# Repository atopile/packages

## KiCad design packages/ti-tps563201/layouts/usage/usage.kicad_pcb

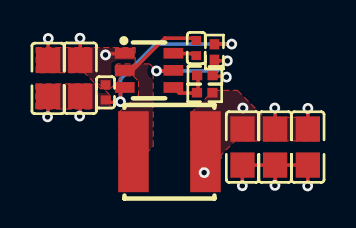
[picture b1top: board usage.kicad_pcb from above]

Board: 2 copper layers, 12 parts (0 on the bottom side), 7 nets.

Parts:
C1, C4: 100nF ±10%; C0402
C2, C3, C5, C6, C7: 10µF ±10%; C0805
L1: L 2.2µH ±20%; IND-SMD_L5.0-W5.0_FNR5012S
R1: 10kΩ ±1%; R0402
R2: 10.2kΩ ±1%; R0402
R3: 3.09kΩ ±1%; R0402
U1: SOT-23-6_L2.9-W1.6-P0.95-LS2.8-BR

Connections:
EN: R1.1, U1.5
hv: C1.1, U1.6
input_caps[2]-power-hv: C2.1, C3.1, C4.1, R1.2, U1.3
lv: C1.2, L1.1, U1.2
output_caps[2]-power-hv: C5.1, C6.1, C7.1, L1.2, R2.1
output_caps[2]-power-lv: C2.2, C3.2, C4.2, C5.2, C6.2, C7.2, R3.2, U1.1
ref_out-hv: R2.2, R3.1, U1.4

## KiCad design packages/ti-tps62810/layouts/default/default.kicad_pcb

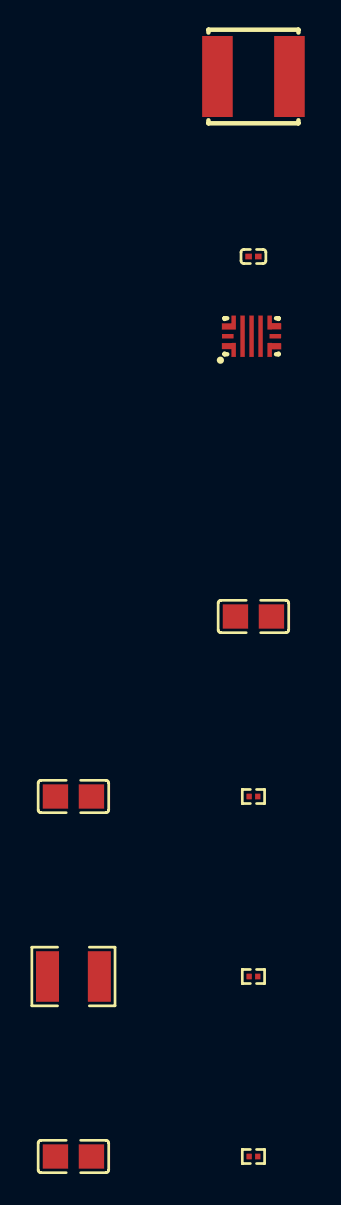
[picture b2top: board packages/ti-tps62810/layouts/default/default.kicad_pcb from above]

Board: 2 copper layers, 10 parts (0 on the bottom side), 7 nets, no tracks yet.

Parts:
C1, C2, C3: 0F; C0805
C4: 0F; C0201
L1: L 0H; IND-SMD_L5.0-W5.0_FNR5012S
R1, R2: 100000Ω; R0201
R3: 200000Ω; R0201
R4: 75Ω; R1210
U1: VQFN-HR-9_L3.0-W2.0-P0.50-BL_TI_TPS6281XXXXX

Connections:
EN: R1.2, U1.8
FB: R2.1, R3.2, U1.5
SW: L1.1, U1.3
hv: C1.1, R1.1, U1.2
lv: C1.2, C2.2, C3.2, C4.2, R2.2, R4.2, U1.4, U1.7
output_cap2-power-hv: C2.1, C3.1, L1.2, R3.1, R4.1
soft_start_cap-power-hv: C4.1, U1.6

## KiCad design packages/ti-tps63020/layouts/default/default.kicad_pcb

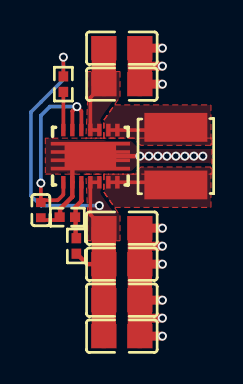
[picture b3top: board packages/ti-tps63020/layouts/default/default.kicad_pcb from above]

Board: 2 copper layers, 12 parts (0 on the bottom side), 9 nets.

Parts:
C1, C2: 10µF ±10%; C0805
C3, C4, C5, C6: 22µF ±20%; C0805
C7: 100nF ±10%; C0402
L1: L 1µH ±20%; IND-SMD_L4.0-W4.0
R1: 102kΩ ±1%; R0402
R2: 34.8kΩ ±1%; R0402
R3: 1MΩ ±1%; R0402
U1: VSON-14_L4.0-W3.0-P0.50-BL-EP_TI_DSJ

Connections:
6: L1.2, U1.6, U1.7
8: L1.1, U1.8, U1.9
PG: R3.1, U1.14
hv: C7.1, U1.1, U1.12, U1.13
input_decoupling_capacitor[1]-power-hv: C1.1, C2.1, U1.10, U1.11
input_decoupling_capacitor[1]-power-lv: C1.2, C2.2, U1.2, U1.15
output_decoupling_capacitor[3]-power-hv: C3.1, C4.1, C5.1, C6.1, R1.1, R3.2, U1.4, U1.5
output_decoupling_capacitor[3]-power-lv: C3.2, C4.2, C5.2, C6.2, R2.2
ref_out-hv: R1.2, R2.1, U1.3

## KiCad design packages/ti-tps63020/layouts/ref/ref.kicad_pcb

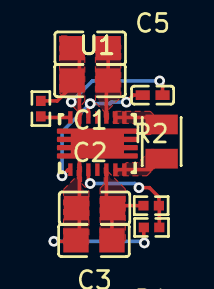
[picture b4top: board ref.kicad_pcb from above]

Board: 2 copper layers, 10 parts (0 on the bottom side), 8 nets.

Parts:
C1, C2, C3, C4: 10µF ±10% 25V X5R; C0805
C5: 100nF ±10% 16V X7R; C0402
R1: 1.8kΩ ±1% 62.5mW; R0402
R2: 10kΩ ±1% 62.5mW; R0402
R3: 1MΩ ±1% 62.5mW; R0402
U1: VSON-14_L4.0-W3.0-P0.50-BL-EP_TI_DSJ
U2: IND-SMD_L2.5-W2.0_WPN252012H

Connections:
EN: C5.1, U1.1, U1.12
FB: R1.1, R2.2, U1.3
L1: U1.8, U1.9, U2.1
L2: U1.6, U1.7, U2.2
PG: R3.1, U1.14
VIN: C1.1, C2.1, U1.10, U1.11
VOUT: C3.1, C4.1, R2.1, U1.4, U1.5
gnd: C1.2, C2.2, C3.2, C4.2, C5.2, R1.2, R3.2, U1.2, U1.13, U1.15
